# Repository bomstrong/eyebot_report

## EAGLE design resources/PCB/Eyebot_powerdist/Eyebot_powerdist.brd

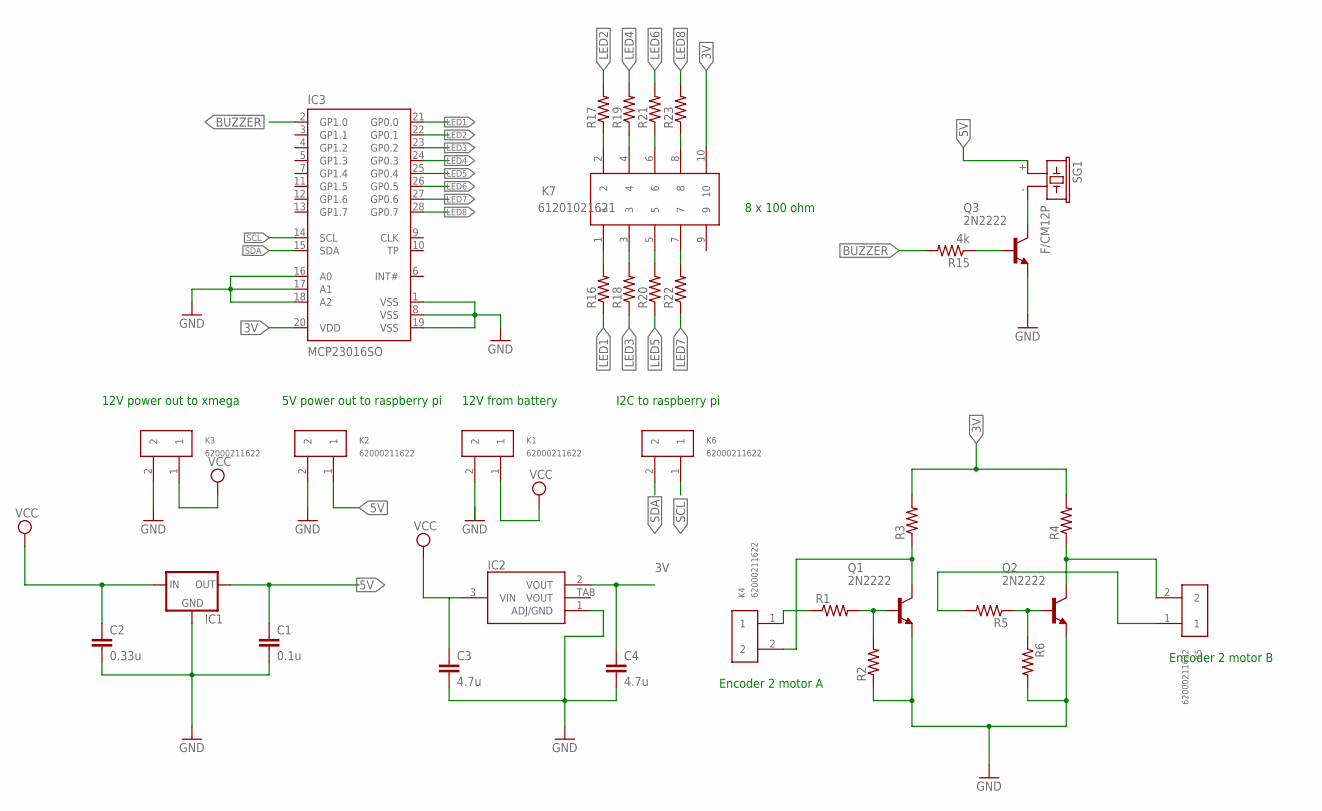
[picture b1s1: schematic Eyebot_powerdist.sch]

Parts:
C1: 0.1u; AXIAL-5MM
C2: 0.33u; CAP-PTH-SMALL
C3, C4: 4.7u; 1206
IC1: V_REG_78XX-TO-220; TO-220-ALT
IC2: LDO1117-SOT223; SOT223-3L
IC3: MCP23016SO; SO-28W
K1, K2, K3, K4, K5, K6: 62000211622
K7: 61201021621
Q1, Q2, Q3: 2N2222; TO18
R1, R2, R3, R4, R5, R6, R16, R17, R18, R19, R20, R21, R22, R23: R-US_0309/10; 0309/10
R15: 4k; 0309/10
SG1: F/CM12P

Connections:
3V: C4.1, IC2.2 (VOUT), IC3.20 (VDD), K7.10, R3.2, R4.2
5V: C1.P$1 (1), IC1.OUT, K2.1, SG1.+ (1)
BUZZER: IC3.2 (GP1.0), R15.2
GND: C1.P$2 (2), C2.2, C3.2, C4.2, IC1.GND, IC2.1 (ADJ/GND), IC3.1 (VSS), IC3.8 (VSS), IC3.16 (A0), IC3.17 (A1), IC3.18 (A2), IC3.19 (VSS), K1.2, K2.2, K3.2, Q1.1 (E), Q2.1 (E), Q3.1 (E), R2.1, R6.2
LED1: IC3.21 (GP0.0), R16.1
LED2: IC3.22 (GP0.1), R17.2
LED3: IC3.23 (GP0.2), R18.1
LED4: IC3.24 (GP0.3), R19.2
LED5: IC3.25 (GP0.4), R20.1
LED6: IC3.26 (GP0.5), R21.2
LED7: IC3.27 (GP0.6), R22.1
LED8: IC3.28 (GP0.7), R23.2
unnamed: Q1.2 (B), R1.2, R2.2
unnamed: K4.2, Q1.3 (C), R3.1
unnamed: K4.1, R1.1
unnamed: K7.2, R17.1
unnamed: Q2.2 (B), R5.1, R6.1
unnamed: K7.4, R19.1
unnamed: K5.1, R5.2
unnamed: K5.2, Q2.3 (C), R4.1
unnamed: K7.6, R21.1
unnamed: K7.8, R23.1
unnamed: K7.7, R22.2
unnamed: K7.5, R20.2
unnamed: K7.3, R18.2
unnamed: K7.1, R16.2
unnamed: Q3.2 (B), R15.1
unnamed: Q3.3 (C), SG1.- (2)
SCL: IC3.14 (SCL), K6.1
SDA: IC3.15 (SDA), K6.2
VCC: C2.1, C3.1, IC1.IN, IC2.3 (VIN), K1.1, K3.1

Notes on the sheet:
5V power out to raspberry pi
12V power out to xmega
12V from battery
Encoder 2 motor A
Encoder 2 motor B
I2C to raspberry pi
8 x 100 ohm

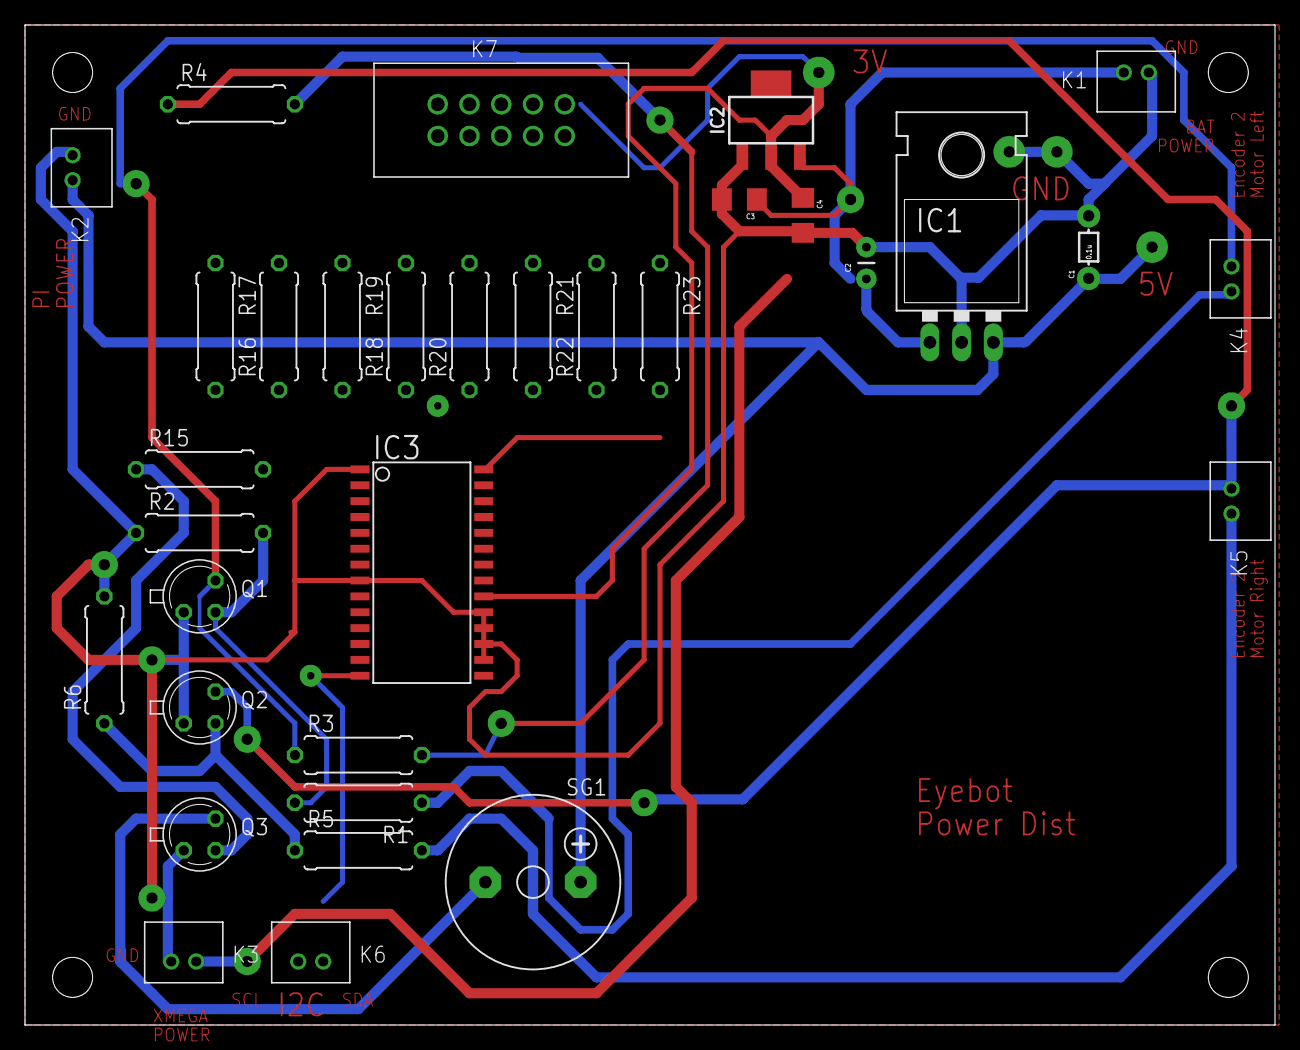
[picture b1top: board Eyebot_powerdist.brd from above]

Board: 2 copper layers, 100.0 x 80.0 mm, 33 parts (0 on the bottom side), 31 nets.

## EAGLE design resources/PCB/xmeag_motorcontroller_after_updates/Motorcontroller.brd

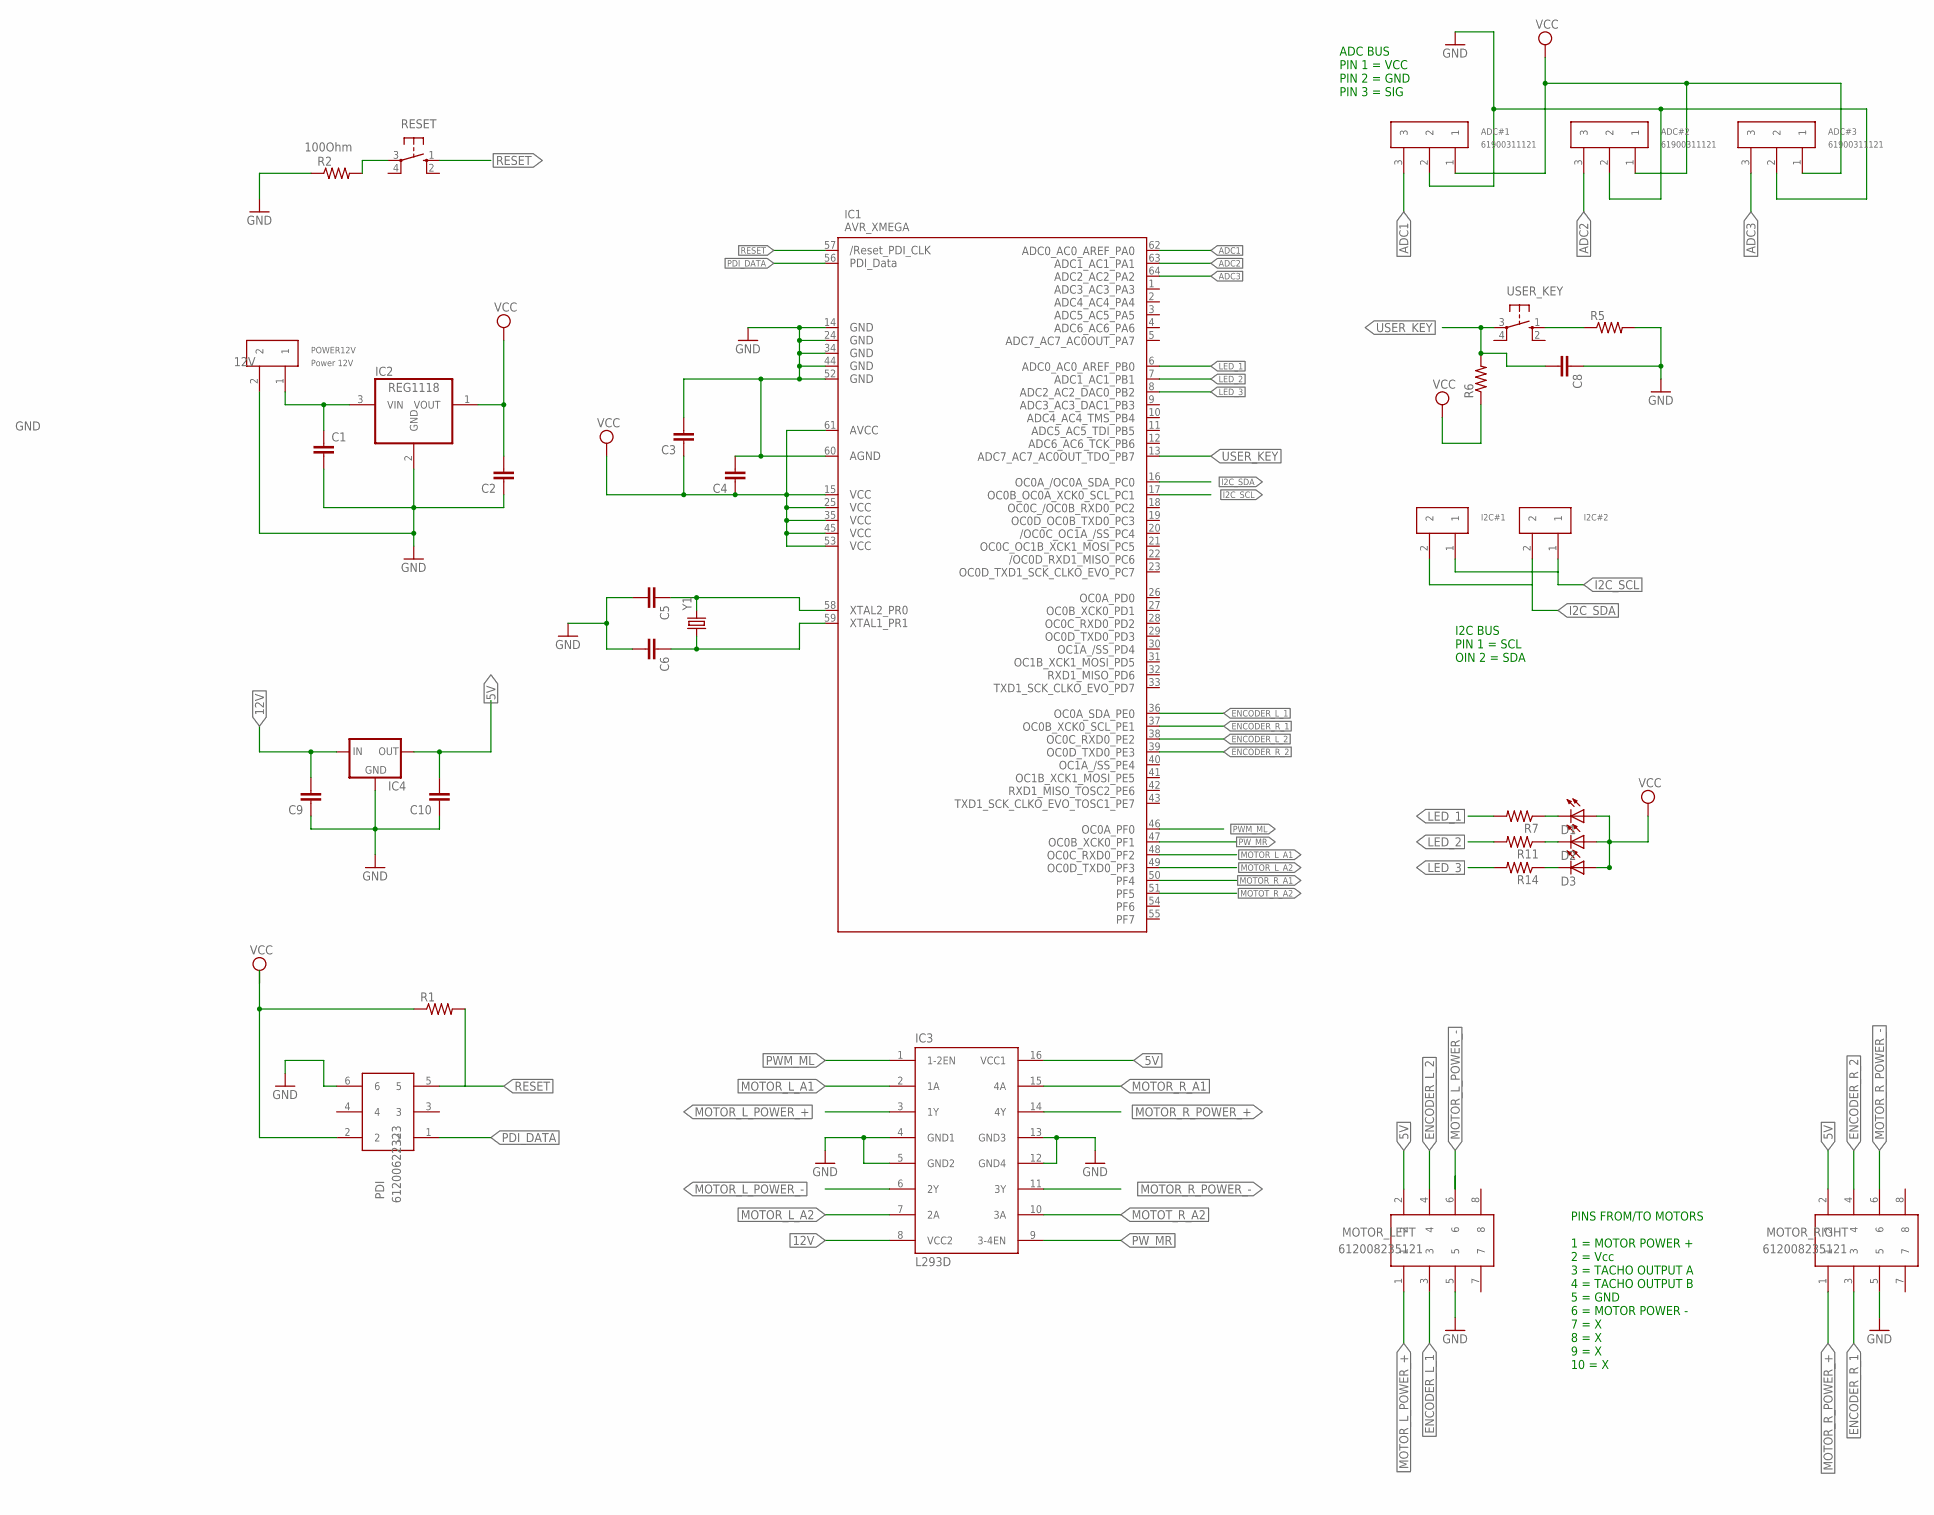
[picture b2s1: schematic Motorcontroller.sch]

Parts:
ADC#1, ADC#2, ADC#3: 61900311121
C1, C2, C3, C4, C5, C6, C8, C9, C10: CAP1206; 1206
D1, D2, D3: LEDSML0805; SML0805
I2C#1, I2C#2: 61900211121
IC1: AVR_XMEGA; TQFP64
IC2: REG1118; SOT223
IC3: L293D; DIL16
IC4: V_REG_78XX-TO-220; TO-220-ALT
MOTOR_LEFT: 612008235121
MOTOR_RIGHT: 612008235121
PDI: 61200622323
POWER12V: Power 12V; 61900211121
R1, R5, R6, R7, R11, R14: RESISTOR1206; 1206
R2: 100Ohm; 1206
RESET: 10-XX; B3F-10XX
USER_KEY: 10-XX; B3F-10XX
Y1: CRYSTALHC49US; HC49US

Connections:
5V: C10.2, IC3.16 (VCC1), IC4.OUT, MOTOR_LEFT.2, MOTOR_RIGHT.2
12V: C1.1, C9.2, IC2.3 (VIN), IC3.8 (VCC2), IC4.IN, POWER12V.1
ADC1: ADC#1.3, IC1.62 (PA0)
ADC2: ADC#2.3, IC1.63 (PA1)
ADC3: ADC#3.3, IC1.64 (PA2)
ENCODER_L_1: IC1.36 (PE0), MOTOR_LEFT.3
ENCODER_L_2: IC1.38 (PE2), MOTOR_LEFT.4
ENCODER_R_1: IC1.37 (PE1), MOTOR_RIGHT.3
ENCODER_R_2: IC1.39 (PE3), MOTOR_RIGHT.4
GND: ADC#1.2, ADC#2.2, ADC#3.2, C1.2, C2.1, C3.2, C4.2, C5.2, C6.2, C8.1, C9.1, C10.1, IC1.14 (GND1), IC1.24 (GND2), IC1.34 (GND3), IC1.44 (GND4), IC1.52 (GND5), IC1.60 (AGND), IC2.2 (GND), IC3.4 (GND1), IC3.5 (GND2), IC3.12 (GND4), IC3.13 (GND3), IC4.GND, MOTOR_LEFT.5, MOTOR_RIGHT.5, PDI.6, POWER12V.2, R2.1, R5.2
I2C_SCL: I2C#1.1, I2C#2.1, IC1.17 (PC1)
I2C_SDA: I2C#1.2, I2C#2.2, IC1.16 (PC0)
LED_1: IC1.6 (PB0), R7.2
LED_2: IC1.7 (PB1)
LED_3: IC1.8 (PB2)
MOTOR_L_A1: IC1.48 (PF2), IC3.2 (1A)
MOTOR_L_A2: IC1.49 (PF3), IC3.7 (2A)
MOTOR_L_POWER_+: IC3.3 (1Y), MOTOR_LEFT.1
MOTOR_L_POWER_-: IC3.6 (2Y), MOTOR_LEFT.6
MOTOR_R_A1: IC1.50 (PF4), IC3.15 (4A)
MOTOR_R_POWER_+: IC3.14 (4Y), MOTOR_RIGHT.1
MOTOR_R_POWER_-: IC3.11 (3Y), MOTOR_RIGHT.6
MOTOT_R_A2: IC1.51 (PF5), IC3.10 (3A)
unnamed: C5.1, IC1.58 (PR0), Y1.2
unnamed: C6.1, IC1.59 (PR1), Y1.1
unnamed: R2.2, RESET.3
unnamed: R5.1, USER_KEY.1 (S)
unnamed: D1.C, R7.1
unnamed: D2.C, R11.1
unnamed: D3.C, R14.1
PDI_DATA: IC1.56 (PDI_DATA), PDI.1
PWM_ML: IC1.46 (PF0), IC3.1 (1-2EN)
PW_MR: IC1.47 (PF1), IC3.9 (3-4EN)
RESET: IC1.57 (RESET), PDI.5, R1.2, RESET.1 (S)
USER_KEY: C8.2, IC1.13 (PB7), R6.2, USER_KEY.3
VCC: ADC#1.1, ADC#2.1, ADC#3.1, C2.2, C3.1, C4.1, D1.A, D2.A, D3.A, IC1.15 (VCC1), IC1.25 (VCC2), IC1.35 (VCC3), IC1.45 (VCC4), IC1.53 (VCC5), IC1.61 (AVCC), IC2.1 (VOUT), PDI.2, R1.1, R6.1

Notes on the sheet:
I2C BUS PIN 1 = SCL OIN 2 = SDA
ADC BUS PIN 1 = VCC PIN 2 = GND PIN 3 = SIG
PINS FROM/TO MOTORS 1 = MOTOR POWER + 2 = Vcc 3 = TACHO OUTPUT A 4 = TACHO OUTPUT B 5 = GND 6 = MOTOR POWER - 7 = X 8 = X 9 = X 10 = X

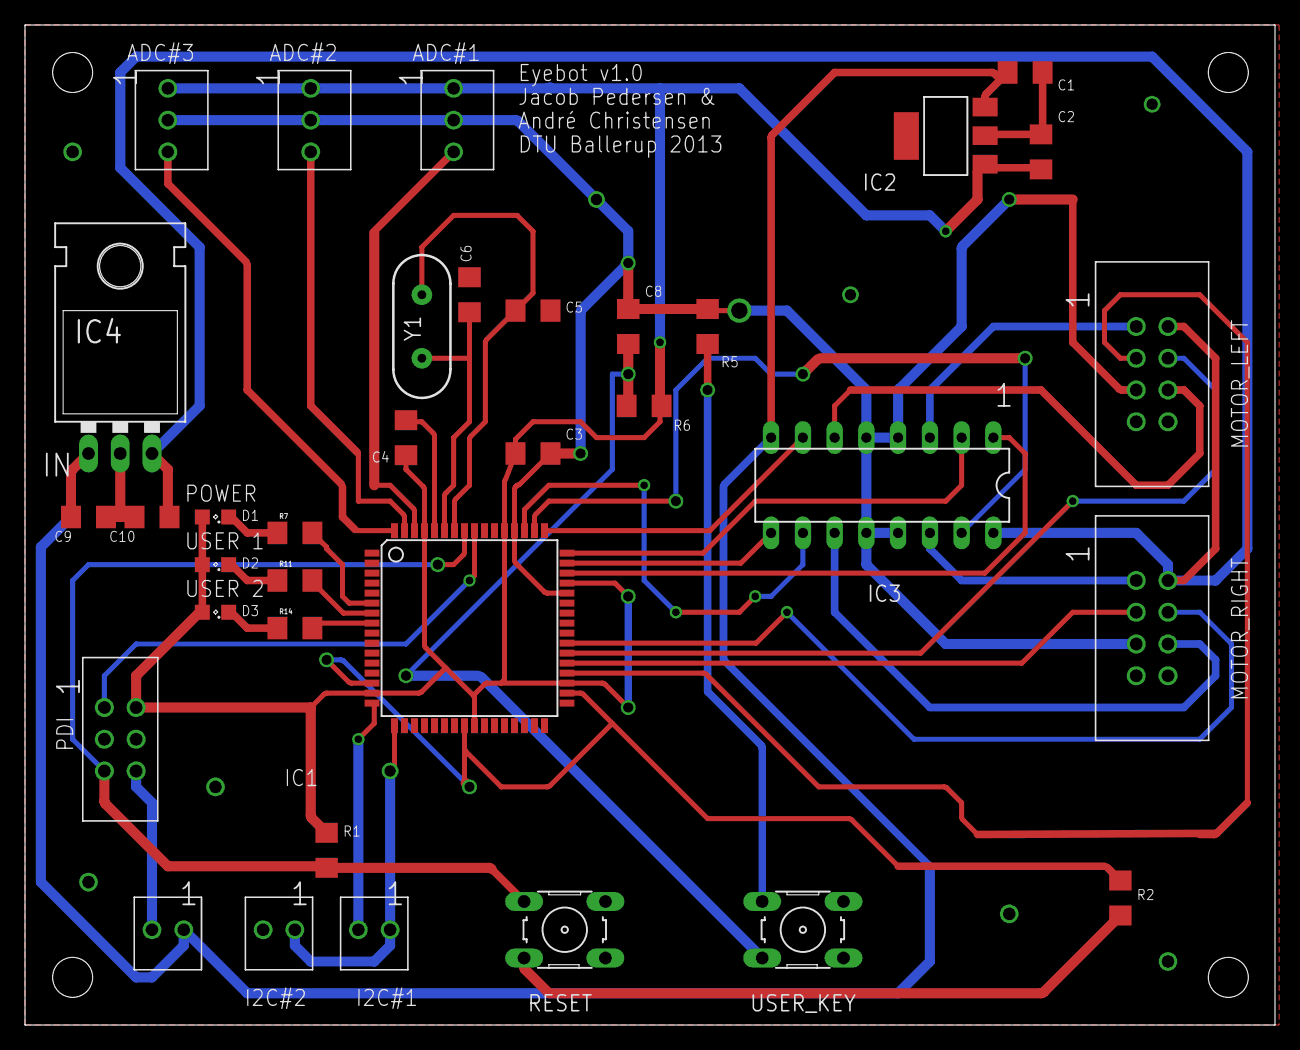
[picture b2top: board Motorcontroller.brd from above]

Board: 2 copper layers, 100.0 x 80.0 mm, 36 parts (0 on the bottom side), 34 nets.

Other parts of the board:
U$3: LOGO2

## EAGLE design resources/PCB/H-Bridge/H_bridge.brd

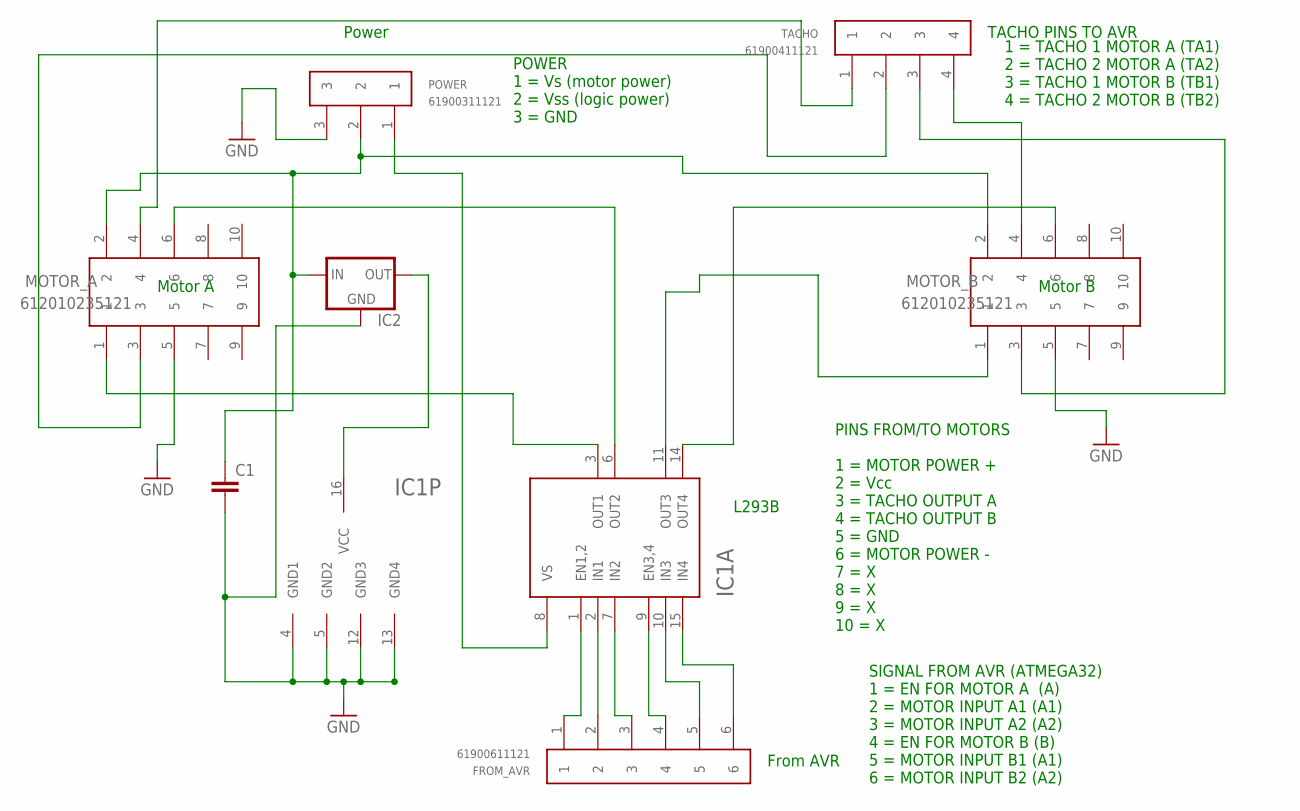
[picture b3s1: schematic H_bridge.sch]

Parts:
C1: C7.5/5; C7.5B5
FROM_AVR: 61900611121
IC1: L293D; DIP16
IC2: V_REG_78XX-TO-220; TO-220-ALT
MOTOR_A: 612010235121
MOTOR_B: 612010235121
POWER: 61900311121
TACHO: 61900411121

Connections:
GND: C1.2, IC1.4 (GND1), IC1.5 (GND2), IC1.12 (GND3), IC1.13 (GND4), IC2.GND, MOTOR_A.5, MOTOR_B.5, POWER.3
unnamed: IC1.3 (OUT1), MOTOR_A.1
unnamed: IC1.6 (OUT2), MOTOR_A.6
unnamed: IC1.11 (OUT3), MOTOR_B.1
unnamed: IC1.14 (OUT4), MOTOR_B.6
unnamed: MOTOR_B.3, TACHO.3
unnamed: IC1.16 (VCC), IC2.OUT
unnamed: C1.1, IC2.IN, MOTOR_A.2, MOTOR_B.2, POWER.2
unnamed: FROM_AVR.1, IC1.1 (EN1,2)
unnamed: FROM_AVR.2, IC1.2 (IN1)
unnamed: FROM_AVR.3, IC1.7 (IN2)
unnamed: FROM_AVR.4, IC1.9 (EN3,4)
unnamed: FROM_AVR.5, IC1.10 (IN3)
unnamed: FROM_AVR.6, IC1.15 (IN4)
unnamed: MOTOR_A.4, TACHO.1
unnamed: MOTOR_A.3, TACHO.2
unnamed: MOTOR_B.4, TACHO.4
unnamed: IC1.8 (VS), POWER.1

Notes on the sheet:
Motor A
Motor B
TACHO PINS TO AVR
Power
From AVR
L293B
POWER 1 = Vs (motor power) 2 = Vss (logic power) 3 = GND
SIGNAL FROM AVR (ATMEGA32) 1 = EN FOR MOTOR A (A) 2 = MOTOR INPUT A1 (A1) 3 = MOTOR INPUT A2 (A2) 4 = EN FOR MOTOR B (B) 5 = MOTOR INPUT B1 (A1) 6 = MOTOR INPUT B2 (A2)
1 = TACHO 1 MOTOR A (TA1) 2 = TACHO 2 MOTOR A (TA2) 3 = TACHO 1 MOTOR B (TB1) 4 = TACHO 2 MOTOR B (TB2)
PINS FROM/TO MOTORS 1 = MOTOR POWER + 2 = Vcc 3 = TACHO OUTPUT A 4 = TACHO OUTPUT B 5 = GND 6 = MOTOR POWER - 7 = X 8 = X 9 = X 10 = X

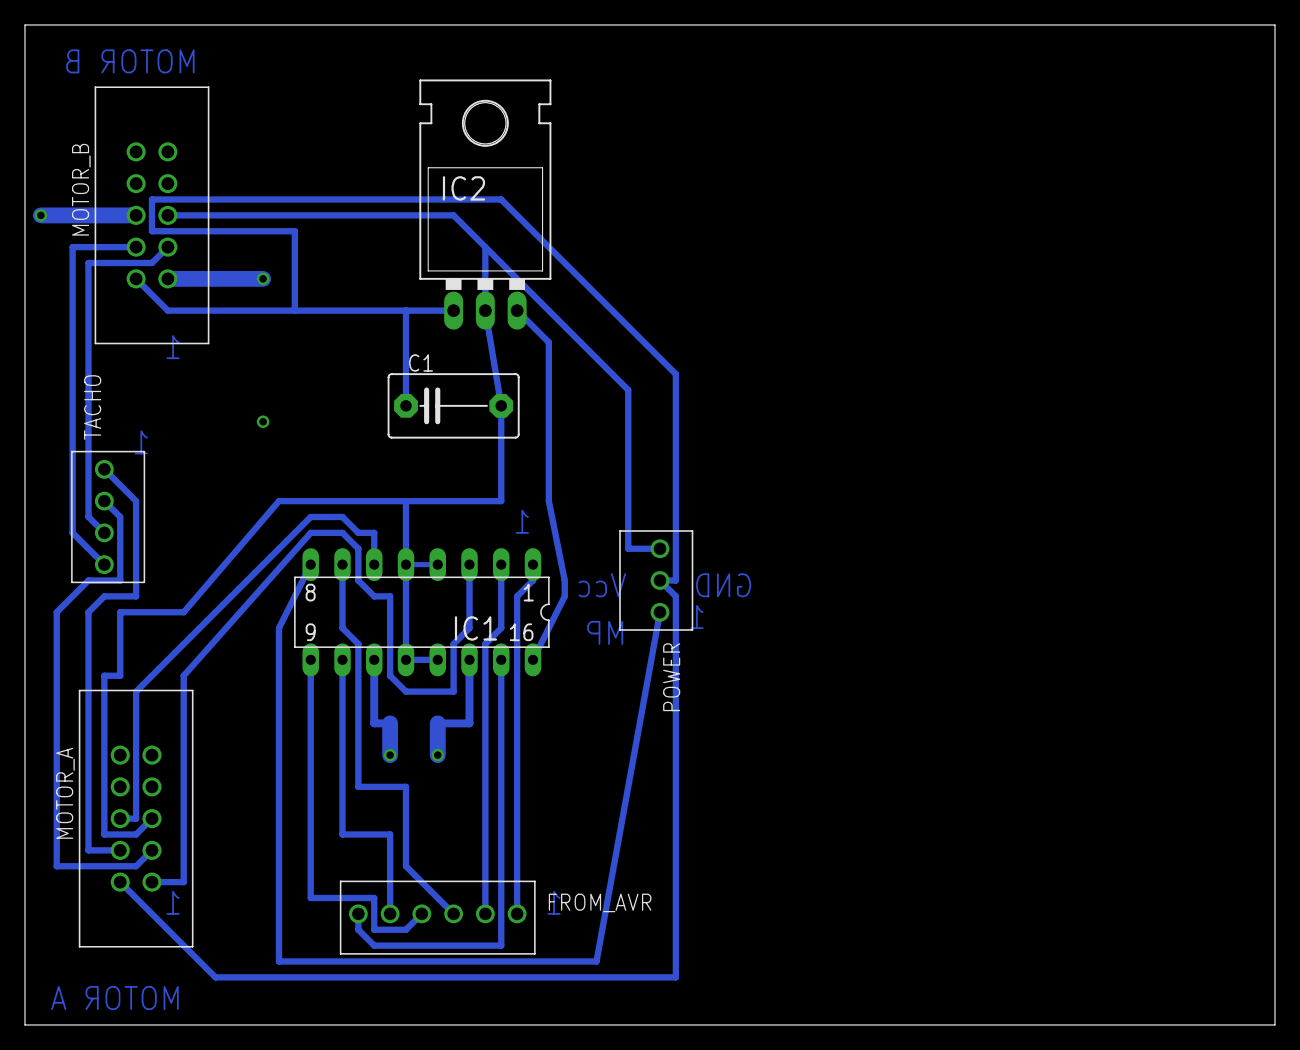
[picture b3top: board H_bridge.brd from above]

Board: 2 copper layers, 100.0 x 80.0 mm, 8 parts (0 on the bottom side), 18 nets.

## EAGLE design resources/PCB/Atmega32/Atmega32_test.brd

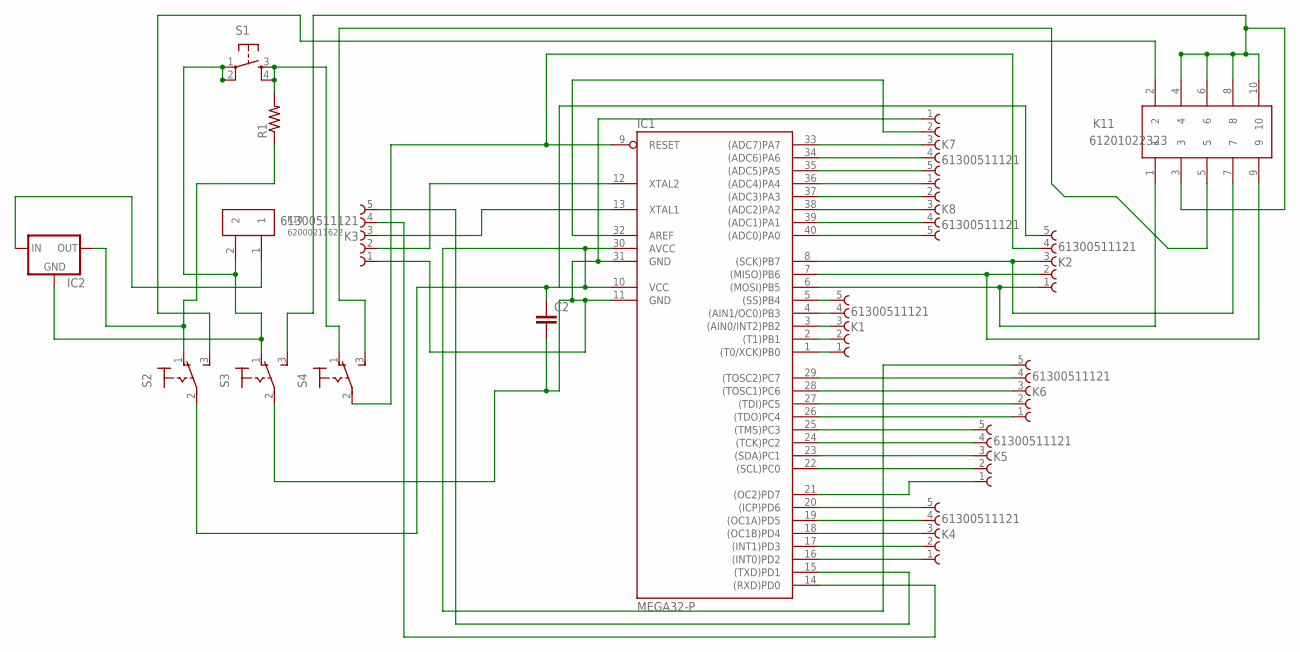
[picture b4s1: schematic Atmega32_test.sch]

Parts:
C2: C10/6; C10B6
IC1: MEGA32-P; DIL40
IC2: V_REG_78XX-TO-220; TO-220-ALT
K1, K2, K3, K4, K5, K6, K7, K8: 61300511121
K10: 62000211622
K11: 61201022323
R1: 10KOHM1/6W5%(PTH)KIT; AXIAL-0.3-KIT
S1: TAC_SWITCHPTH; TACTILE-PTH
S2, S3, S4: 320-916

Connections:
unnamed: IC1.12 (XTAL2), K3.2
unnamed: IC1.26 ((TDO)PC4), K6.1
unnamed: IC1.1 ((T0/XCK)PB0), K1.1
unnamed: IC1.5 ((SS)PB4), K1.5
unnamed: IC1.3 ((AIN0/INT2)PB2), K1.3
unnamed: IC1.4 ((AIN1/OC0)PB3), K1.4
unnamed: IC1.2 ((T1)PB1), K1.2
unnamed: IC1.6 ((MOSI)PB5), K2.1, K11.1
unnamed: IC1.7 ((MISO)PB6), K2.2, K11.9
unnamed: IC1.8 ((SCK)PB7), K2.3, K11.7
unnamed: IC1.39 ((ADC1)PA1), K8.4
unnamed: C2.2, IC1.11 (GND), IC1.31 (GND), K3.1, K7.1, S3.2
unnamed: IC1.9 (RESET), K2.4, S4.2
unnamed: K11.2, S2.3 (S)
unnamed: IC1.14 ((RXD)PD0), K3.4
unnamed: IC2.IN, K10.1
unnamed: IC1.17 ((INT1)PD3), K4.2
unnamed: IC1.16 ((INT0)PD2), K4.1
unnamed: IC1.18 ((OC1B)PD4), K4.3
unnamed: IC1.19 ((OC1A)PD5), K4.4
unnamed: IC1.20 ((ICP)PD6), K4.5
unnamed: IC1.21 ((OC2)PD7), K5.1
unnamed: IC1.22 ((SCL)PC0), K5.2
unnamed: IC1.23 ((SDA)PC1), K5.3
unnamed: IC1.24 ((TCK)PC2), K5.4
unnamed: IC1.25 ((TMS)PC3), K5.5
unnamed: IC1.27 ((TDI)PC5), K6.2
unnamed: IC1.28 ((TOSC1)PC6), K6.3
unnamed: IC1.29 ((TOSC2)PC7), K6.4
unnamed: IC1.13 (XTAL1), K3.3
unnamed: IC1.32 (AREF), K7.2
unnamed: IC1.36 ((ADC4)PA4), K8.1
unnamed: IC1.33 ((ADC7)PA7), K7.3
unnamed: IC1.34 ((ADC6)PA6), K7.4
unnamed: IC1.35 ((ADC5)PA5), K7.5
unnamed: IC1.37 ((ADC3)PA3), K8.2
unnamed: IC1.38 ((ADC2)PA2), K8.3
unnamed: IC1.40 ((ADC0)PA0), K8.5
unnamed: IC2.OUT, R1.P$1 (1), S2.1 (O)
unnamed: R1.P$2 (2), S1.3, S1.4, S4.1 (O)
unnamed: K11.3, K11.4, K11.6, K11.8, K11.10, S3.3 (S)
unnamed: IC2.GND, K10.2, S1.1, S1.2, S3.1 (O)
unnamed: K11.5, S4.3 (S)
unnamed: IC1.15 ((TXD)PD1), K3.5
unnamed: C2.1, IC1.10 (VCC), IC1.30 (AVCC), K2.5, K6.5, S2.2

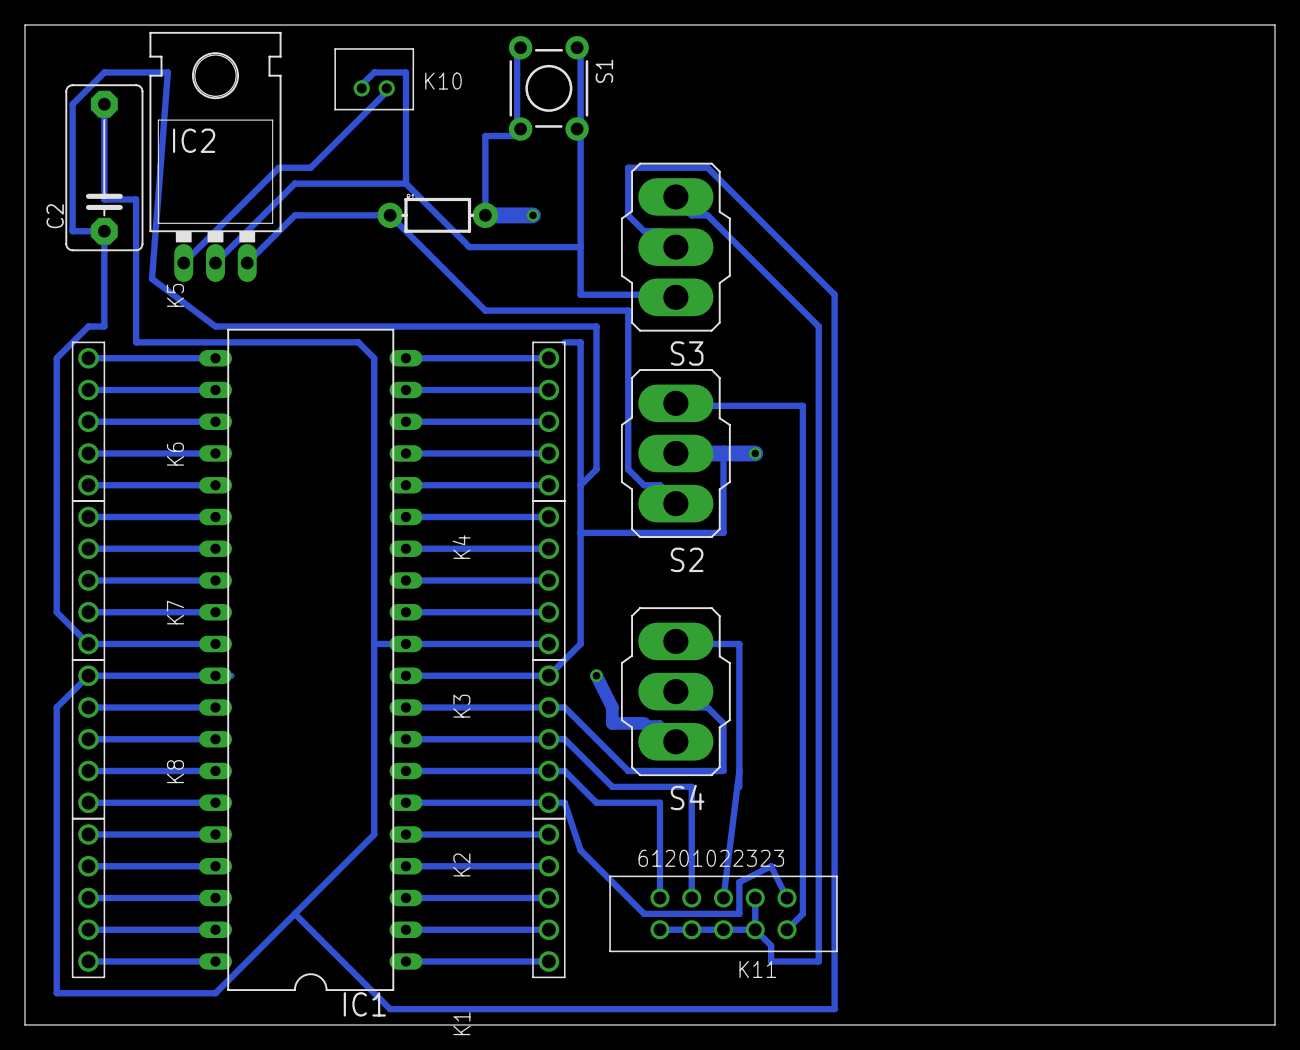
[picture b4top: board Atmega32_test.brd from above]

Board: 2 copper layers, 100.0 x 80.0 mm, 18 parts (0 on the bottom side), 45 nets.

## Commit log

2013-12-14 Remove auto generated files.
2013-12-14 added pcb to resources
2013-12-14 old pcbs added to resources
2013-12-14 xmega pcb updates added to resources
2013-12-14 Chapter 2 - camera.
2013-12-14 Updated references, and changed headings for control chapter.
2013-12-15 IR sensor chapter + key words in i2c chapter
2013-12-15 i2c chapter
2013-12-15 Control chapter.
2013-12-16 from bom
2013-12-16 Conclusion and other stuff.
2013-12-16 Minor changes.
2013-12-17 Simulink files
2013-12-20 lidt rettelser her og der

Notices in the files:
parts and their libraries:
Wuerth_Elektronik_eiCan_01_Pin__Socked_H: Copyright: Würth Elektronik
SparkFun-Electromechanical: Licensing: CC v3.0 Share-Alike You are welcome to use this library for commercial purposes.
